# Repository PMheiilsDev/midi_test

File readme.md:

# Midi Controller for Voicemeeter with rp2040

# Setting up Voicemeeter 

 - Menu -> Midi Mapping 
   - Select 'Tiny USB Device' as Input and Output 
   - Use Learn to setup the Buttons or sliders 
   - Press the 'F'-Button so that it is blue 

# Some Comments might be German and English

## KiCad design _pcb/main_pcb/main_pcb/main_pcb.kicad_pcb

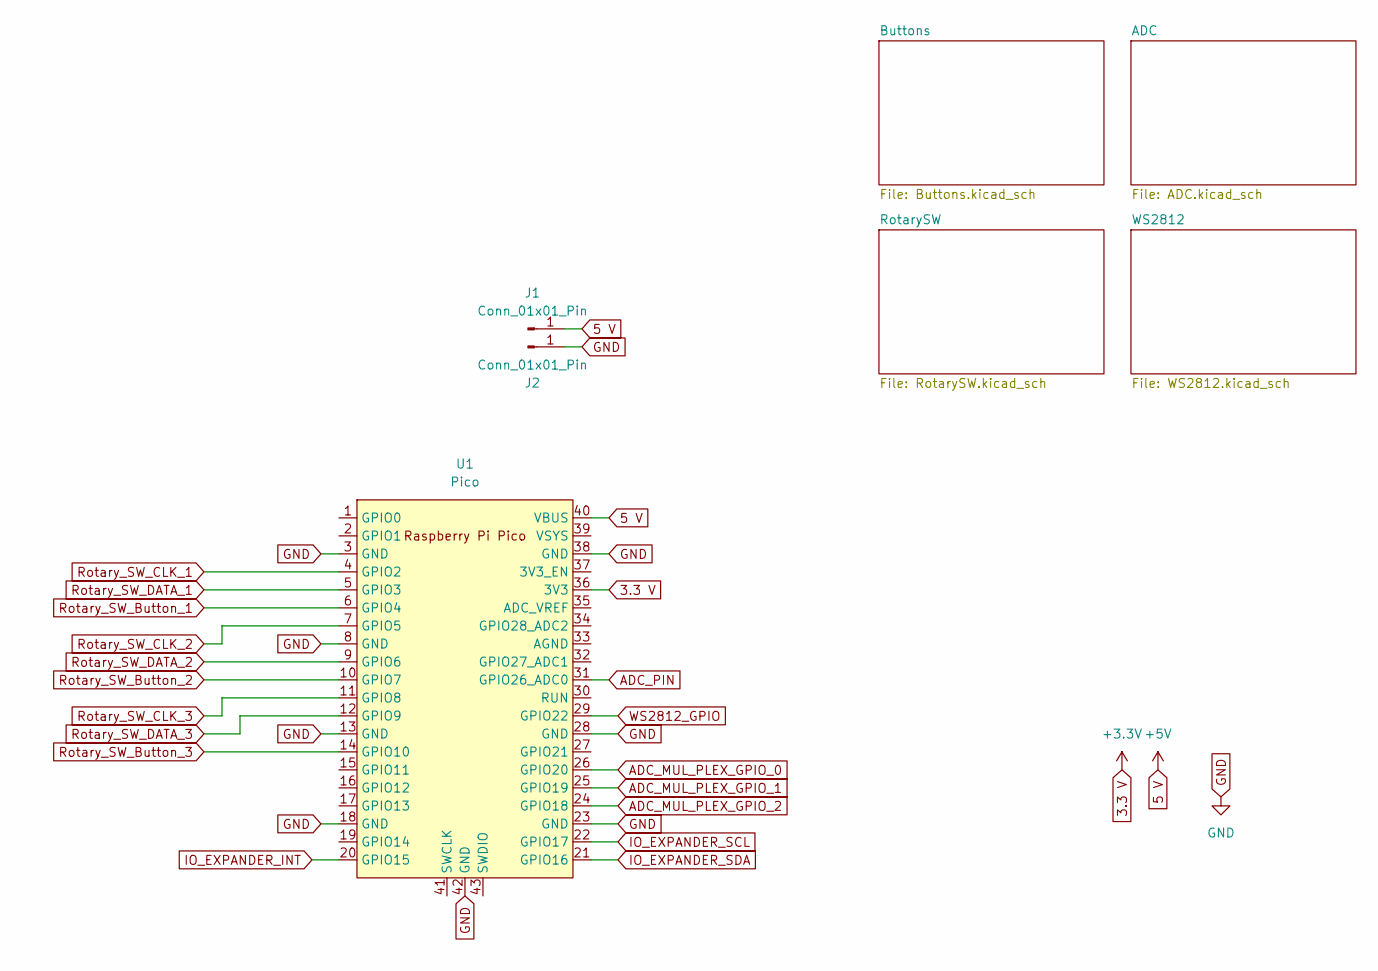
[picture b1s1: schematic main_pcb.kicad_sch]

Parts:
J1, J2: Conn_01x01_Pin; TestPoint_Pad_3.0x3.0mm
U1: Pico; RPi_Pico_SMD_TH

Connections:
3.3 V: U1.36 (3V3); also elsewhere on the board
5 V: J1.1, U1.40 (VBUS); also elsewhere on the board
ADC_MUL_PLEX_GPIO_0: U1.26 (GPIO20); also elsewhere on the board
ADC_MUL_PLEX_GPIO_1: U1.25 (GPIO19); also elsewhere on the board
ADC_MUL_PLEX_GPIO_2: U1.24 (GPIO18); also elsewhere on the board
ADC_PIN: U1.31 (GPIO26_ADC0); also elsewhere on the board
GND: J2.1, U1.3 (GND), U1.8 (GND), U1.13 (GND), U1.18 (GND), U1.23 (GND), U1.28 (GND), U1.38 (GND), U1.42 (GND); also elsewhere on the board
IO_EXPANDER_INT: U1.20 (GPIO15); also elsewhere on the board
IO_EXPANDER_SCL: U1.22 (GPIO17); also elsewhere on the board
IO_EXPANDER_SDA: U1.21 (GPIO16); also elsewhere on the board
Rotary_SW_Button_1: U1.6 (GPIO4); also elsewhere on the board
Rotary_SW_Button_2: U1.10 (GPIO7); also elsewhere on the board
Rotary_SW_Button_3: U1.14 (GPIO10); also elsewhere on the board
Rotary_SW_CLK_1: U1.4 (GPIO2); also elsewhere on the board
Rotary_SW_CLK_2: U1.7 (GPIO5); also elsewhere on the board
Rotary_SW_CLK_3: U1.11 (GPIO8); also elsewhere on the board
Rotary_SW_DATA_1: U1.5 (GPIO3); also elsewhere on the board
Rotary_SW_DATA_2: U1.9 (GPIO6); also elsewhere on the board
Rotary_SW_DATA_3: U1.12 (GPIO9); also elsewhere on the board
WS2812_GPIO: U1.29 (GPIO22); also elsewhere on the board

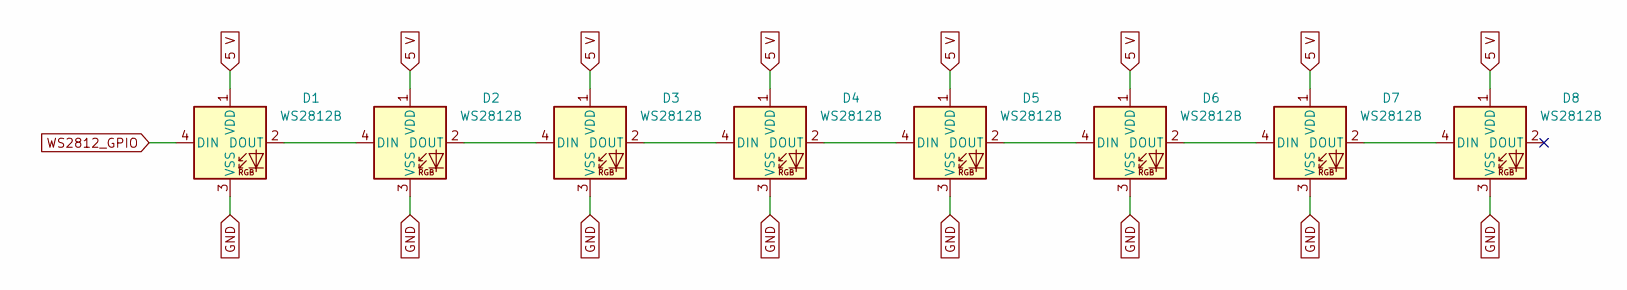
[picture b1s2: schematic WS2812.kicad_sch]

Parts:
D1, D2, D3, D4, D5, D6, D7, D8: WS2812B; LED_WS2812B_PLCC4_5.0x5.0mm_P3.2mm

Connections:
5 V: D1.1 (VDD), D2.1 (VDD), D3.1 (VDD), D4.1 (VDD), D5.1 (VDD), D6.1 (VDD), D7.1 (VDD), D8.1 (VDD); also elsewhere on the board
GND: D1.3 (VSS), D2.3 (VSS), D3.3 (VSS), D4.3 (VSS), D5.3 (VSS), D6.3 (VSS), D7.3 (VSS), D8.3 (VSS); also elsewhere on the board
unnamed: D1.2 (DOUT), D2.4 (DIN)
unnamed: D2.2 (DOUT), D3.4 (DIN)
unnamed: D3.2 (DOUT), D4.4 (DIN)
unnamed: D4.2 (DOUT), D5.4 (DIN)
unnamed: D5.2 (DOUT), D6.4 (DIN)
unnamed: D6.2 (DOUT), D7.4 (DIN)
unnamed: D7.2 (DOUT), D8.4 (DIN)
WS2812_GPIO: D1.4 (DIN); also elsewhere on the board

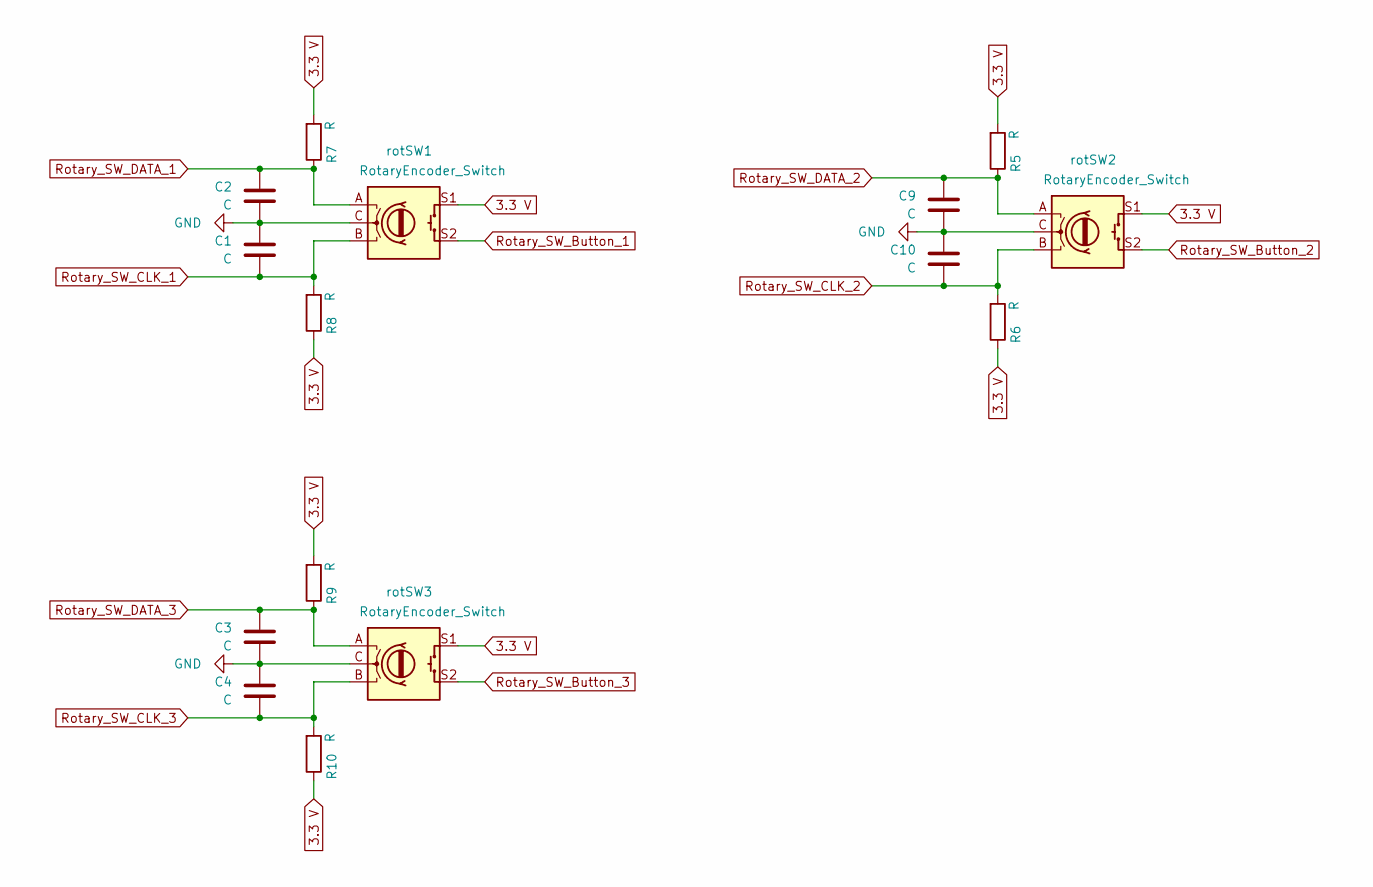
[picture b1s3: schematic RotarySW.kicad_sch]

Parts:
C1, C2, C3, C4, C9, C10: C; C_1206_3216Metric
R5, R6, R7, R8, R9, R10: R; R_1206_3216Metric
rotSW1, rotSW2, rotSW3: RotaryEncoder_Switch; RotaryEncoder_Alps_EC11E-Switch_Vertical_H20mm

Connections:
3.3 V: R5.2, R6.1, R7.2, R8.1, R9.2, R10.1, rotSW1.S1, rotSW2.S1, rotSW3.S1; also elsewhere on the board
GND: C1.1, C2.2, C3.2, C4.1, C9.2, C10.1, rotSW1.C, rotSW2.C, rotSW3.C; also elsewhere on the board
Rotary_SW_Button_1: rotSW1.S2; also elsewhere on the board
Rotary_SW_Button_2: rotSW2.S2; also elsewhere on the board
Rotary_SW_Button_3: rotSW3.S2; also elsewhere on the board
Rotary_SW_CLK_1: C1.2, R8.2, rotSW1.B; also elsewhere on the board
Rotary_SW_CLK_2: C10.2, R6.2, rotSW2.B; also elsewhere on the board
Rotary_SW_CLK_3: C4.2, R10.2, rotSW3.B; also elsewhere on the board
Rotary_SW_DATA_1: C2.1, R7.1, rotSW1.A; also elsewhere on the board
Rotary_SW_DATA_2: C9.1, R5.1, rotSW2.A; also elsewhere on the board
Rotary_SW_DATA_3: C3.1, R9.1, rotSW3.A; also elsewhere on the board

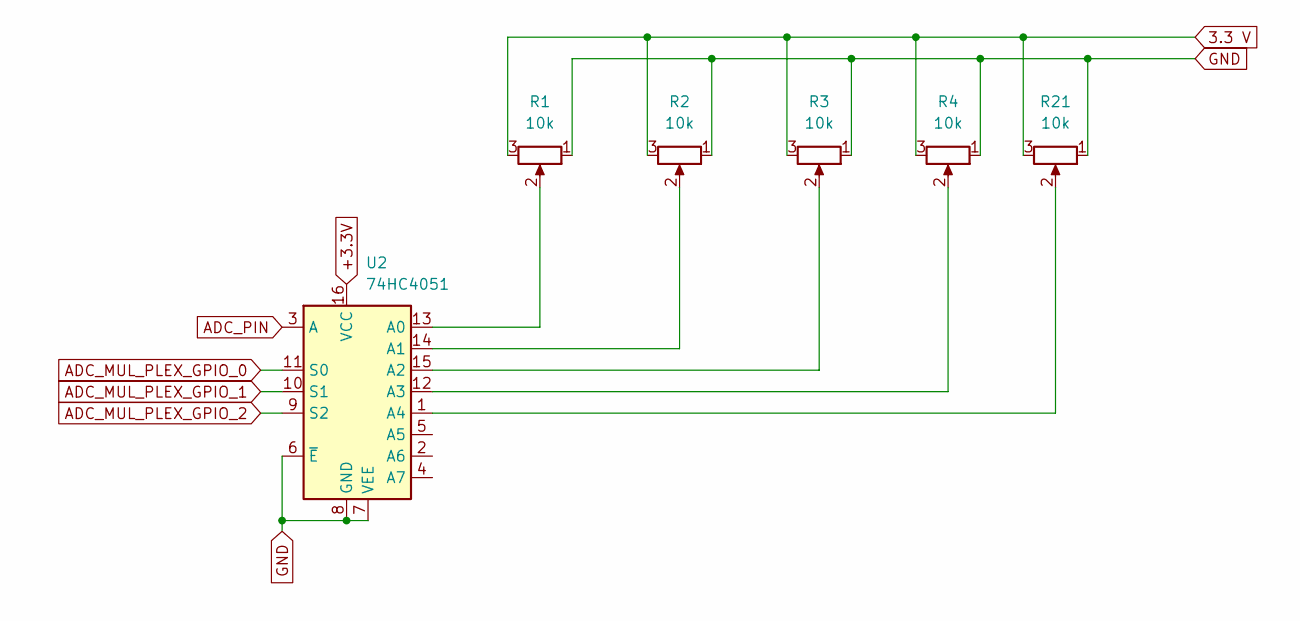
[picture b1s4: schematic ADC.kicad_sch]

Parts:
R1, R2, R3, R4, R21: 10k; Linear_Potentiometer
U2: 74HC4051; DIP-16_W7.62mm

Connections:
3.3 V: R1.3, R2.3, R3.3, R4.3, R21.3, U2.16 (VCC); also elsewhere on the board
ADC_MUL_PLEX_GPIO_0: U2.11 (S0); also elsewhere on the board
ADC_MUL_PLEX_GPIO_1: U2.10 (S1); also elsewhere on the board
ADC_MUL_PLEX_GPIO_2: U2.9 (S2); also elsewhere on the board
ADC_PIN: U2.3 (A); also elsewhere on the board
GND: R1.1, R2.1, R3.1, R4.1, R21.1, U2.6 (~E), U2.7 (VEE), U2.8 (GND); also elsewhere on the board
unnamed: R1.2, U2.13 (A0)
unnamed: R2.2, U2.14 (A1)
unnamed: R3.2, U2.15 (A2)
unnamed: R4.2, U2.12 (A3)
unnamed: R21.2, U2.1 (A4)

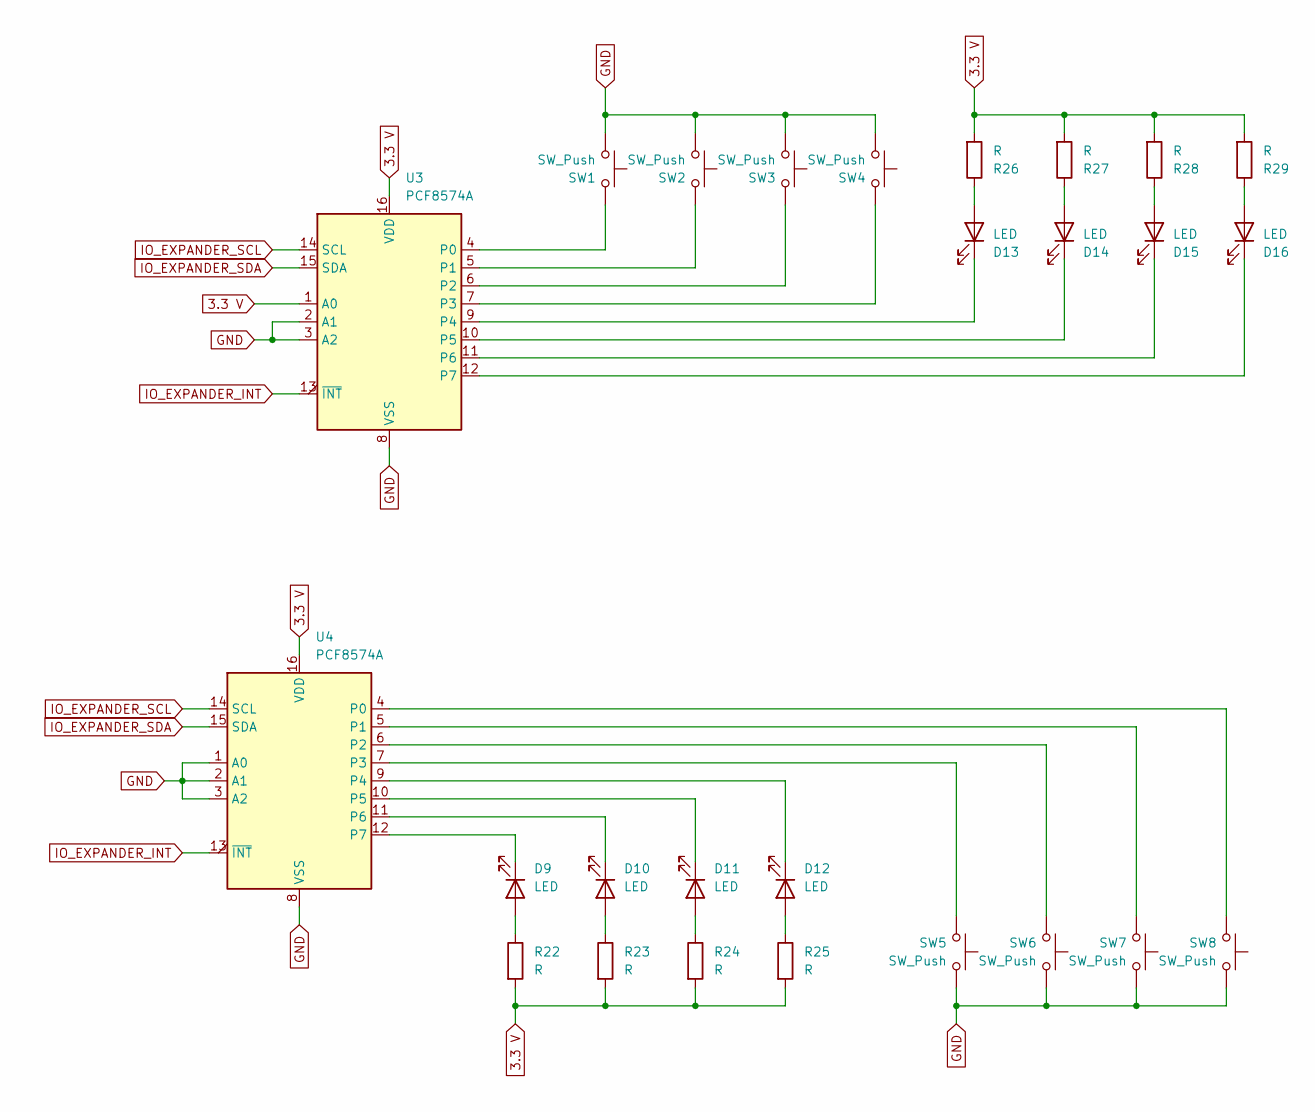
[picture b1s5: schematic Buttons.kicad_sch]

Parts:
D9, D10, D11, D12, D13, D14, D15, D16: LED; LED_Rectangular_W3.9mm_H1.9mm
R22, R23, R24, R25, R26, R27, R28, R29: R; L_1206_3216Metric_Pad1.22x1.90mm_HandSolder
SW1, SW2, SW3, SW4, SW5, SW6, SW7, SW8: SW_Push; SW_Cherry_MX_1.00u_Plate
U3, U4: PCF8574A; DIP-16_W7.62mm

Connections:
3.3 V: R22.2, R23.2, R24.2, R25.2, R26.2, R27.2, R28.2, R29.2, U3.1 (A0), U3.16 (VDD), U4.16 (VDD); also elsewhere on the board
GND: SW1.1, SW2.1, SW3.1, SW4.1, SW5.1, SW6.1, SW7.1, SW8.1, U3.2 (A1), U3.3 (A2), U3.8 (VSS), U4.1 (A0), U4.2 (A1), U4.3 (A2), U4.8 (VSS); also elsewhere on the board
IO_EXPANDER_INT: U3.13 (~INT), U4.13 (~INT); also elsewhere on the board
IO_EXPANDER_SCL: U3.14 (SCL), U4.14 (SCL); also elsewhere on the board
IO_EXPANDER_SDA: U3.15 (SDA), U4.15 (SDA); also elsewhere on the board
unnamed: D9.2 (A), R22.1
unnamed: D9.1 (K), U4.12 (P7)
unnamed: D10.2 (A), R23.1
unnamed: D10.1 (K), U4.11 (P6)
unnamed: D11.2 (A), R24.1
unnamed: D11.1 (K), U4.10 (P5)
unnamed: D12.2 (A), R25.1
unnamed: D12.1 (K), U4.9 (P4)
unnamed: D13.2 (A), R26.1
unnamed: D13.1 (K), U3.9 (P4)
unnamed: D14.2 (A), R27.1
unnamed: D14.1 (K), U3.10 (P5)
unnamed: D15.2 (A), R28.1
unnamed: D15.1 (K), U3.11 (P6)
unnamed: D16.2 (A), R29.1
unnamed: D16.1 (K), U3.12 (P7)
unnamed: SW1.2, U3.4 (P0)
unnamed: SW2.2, U3.5 (P1)
unnamed: SW3.2, U3.6 (P2)
unnamed: SW4.2, U3.7 (P3)
unnamed: SW8.2, U4.4 (P0)
unnamed: SW7.2, U4.5 (P1)
unnamed: SW6.2, U4.6 (P2)
unnamed: SW5.2, U4.7 (P3)

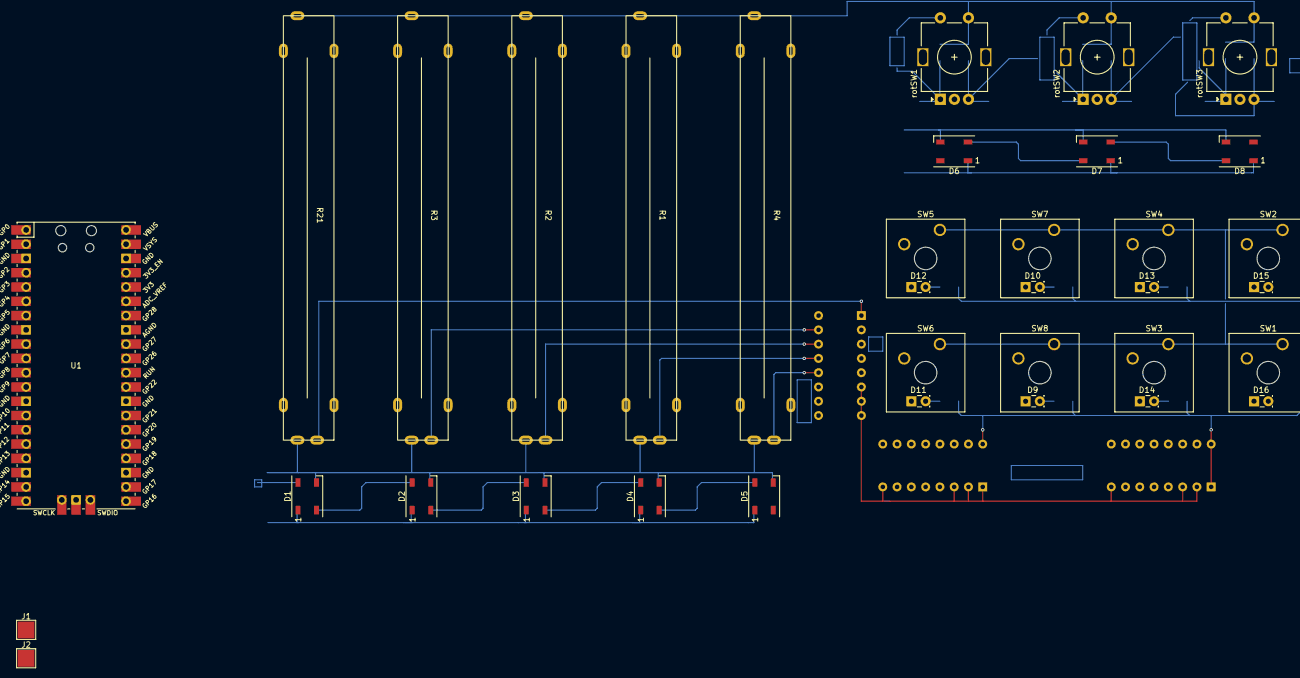
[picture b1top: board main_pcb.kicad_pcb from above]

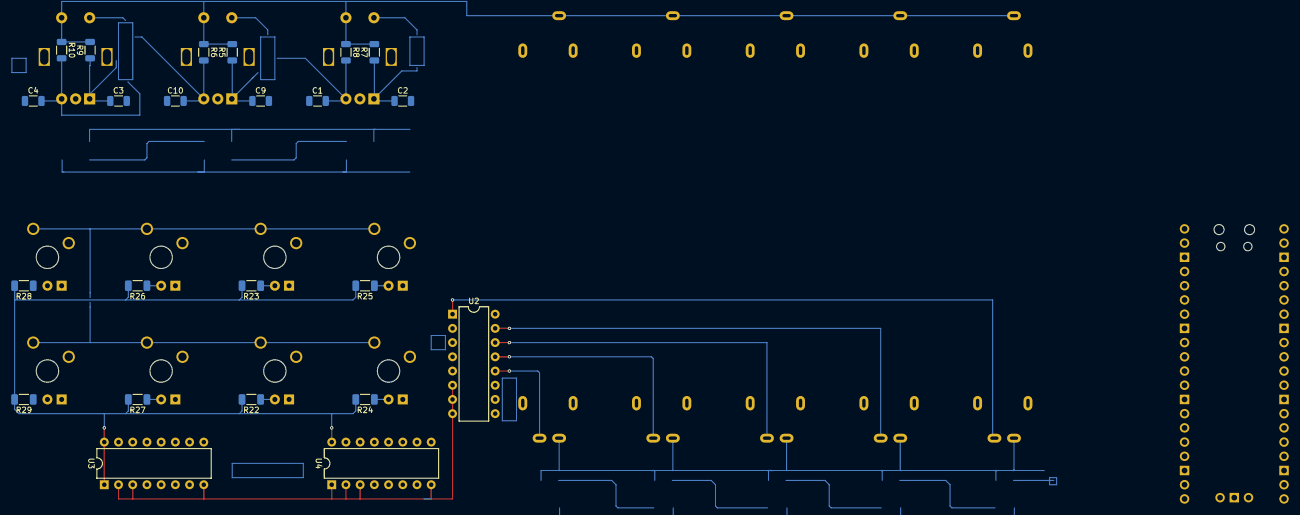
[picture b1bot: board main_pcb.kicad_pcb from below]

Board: 2 copper layers, 58 parts (23 on the bottom side), 56 nets.

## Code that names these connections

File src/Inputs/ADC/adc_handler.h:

#ifndef _ADC_HANDLER_H
#define _ADC_HANDLER_H

#include <inttypes.h>
#include <stdbool.h>

#include "hardware/gpio.h"
#include "hardware/adc.h"


#include "hardware/pwm.h"
#include "tusb.h"

#define MAX_ADC_CHANNELS 5
#define ADC_MUL_LAST_REF_AMT_BITS 4
#define ADC_MUL_LAST_REF_AMT (1 << ADC_MUL_LAST_REF_AMT_BITS) 

#define ADC_MUL_PLEX_GPIO_0 21
#define ADC_MUL_PLEX_GPIO_1 20
#define ADC_MUL_PLEX_GPIO_2 19

typedef struct 
{
    uint8_t pin;
    uint8_t note;
    uint8_t is_mul_plex: 1, mul_plex_channel : 3; // assuming that the multiplexer has 3 pins for channel selection 
    uint8_t mul_plex[3];
    uint16_t result;
    uint16_t result_pref; 
    uint8_t res_7_bit;
    uint8_t num_reads;
} 
adc_channel_t;

extern adc_channel_t adc_channels[MAX_ADC_CHANNELS];

/// @brief setting up all necessary ADCs from cdc_channels and starting timer to call adc_task 
void adc_setup(void);

/// @brief handling next ADC from adc_channels 
bool adc_task( repeating_timer_t *rt );

/// @brief converting a GPIO pin to an ADC channel 
/// @param gpio GPIO pin number 
/// @return ADC channel number 
static inline int gpio_to_adc_channel(uint gpio);

/// @brief set the value of the gpio pins set in the adc_channel
/// @param adc_channel pointer to the adc_channel_t 
void adc_set_mul_plex_gpios( adc_channel_t *adc_channel );

#endif


// ADC ideas
// create a reapeating timer and read the adc value every so often
//
// create a function that can simulate a Highpass filter by interpolating 
// filter values that are off from average 
//  - this might make add delay


// ADC TODO 
// - add support for using analog multiplexer to read multiple analog inputs

// ((( it might be possible to check if a multiplexer is connected by connecting one of the 8 channels to a fixed level )))

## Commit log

2024-11-20 example working
2024-11-21 first test working
2024-11-21 working adc to pwm ; not working in voice meeter
2024-11-22 some changes to timings
2024-11-23 working with hardware debounce
2024-11-29 debugger working
2024-11-29 removed map function
2025-02-09 added gitignore file
2025-02-09 gitignore build
2025-02-09 added readme file
2025-02-09 todo file
2025-02-09 todo list update
2025-02-09 Button init
2025-02-09 Button doing nothing yet
2025-02-09 rotary sw fixes removed feedback
2025-02-09 Changed so that range of poti can be used for usefull area
2025-02-09 added input reader with python
2025-02-09 added midi send to rp2040 tests
2025-02-09 does recieve something with voicemeeter
2025-02-09 uart debugging not working
2025-02-09 see todo updated to test feedback to rp2040 with voicemeeter
2025-02-14 ui program with chatgpt
2025-02-14 changed updating of dropdown lists
2025-02-14 not as i want it to be
2025-02-14 refresh buttons not scaling
2025-02-14 selecting works when only one present
2025-02-14 adding input device change message
2025-02-14 changed to use text and dupe when one
2025-02-14 using the activated works at all changes
2025-02-14 device selection working
2025-02-14 added #regions but listner no longer working
2025-02-14 one region added
2025-02-14 added [ -> ] and [ <- ]
2025-02-14 clear button
2025-02-14 made it bolt
2025-02-14 Disconnect Buttons
2025-02-14 both disconnects working
2025-02-14 todo
2025-02-15 why not working
2025-02-15 was working just had to replug
2025-02-27 logging the data as strings
2025-02-27 readme
2025-02-28 move main c file
2025-02-28 moved rot sw functions to own files
2025-02-28 variabels added
2025-02-28 fixed error
2025-02-28 moved midi handler to other files
2025-02-28 moved adc handler
2025-02-28 renamed folder
2025-02-28 moved to new files
2025-02-28 moved led functions
2025-02-28 changed to led handler
2025-02-28 changed adc scaling
2025-03-02 led setup functions
2025-03-02 process all up/ down interupts for rotary sw
2025-03-02 extended to more than one rot sw switch with AI
2025-03-02 foramtion and to const uint = 2
2025-03-02 working
2025-03-03 gpio to adc channel
2025-03-03 ideas update average implementation
2025-03-04 added ws2812 files
2025-03-04 ws2812 testing timing
2025-03-05 testing reset time
2025-03-05 added usefull ws2812 handler functions and structs
2025-03-05 removed tests from init
2025-03-07 changed to update at ever change not only every second
2025-03-07 removed pwm pin
2025-03-07 changed to work with multiple adc pins
2025-03-07 added comments
2025-03-07 added adc multiplexer support initialisation
2025-03-07 added multiplexer function to adc_task
2025-03-07 todo added note
2025-03-07 added to header file
2025-03-08 testing how long a loop takes .5 ms without adc sleep time
2025-03-08 added kiCAD Project
2025-03-08 added lib for mx switches
2025-03-08 added own footprint lib for potentiometer
2025-03-08 added libraries to project
2025-03-08 changed to work with relative paths
2025-03-08 added cache file to gitignore
2025-03-08 added .zip files to git ignore
2025-03-08 automatic changes by kicad
2025-03-08 added pi pico footprint library
2025-03-08 changed to rel path
2025-03-08 added pi pico symbol from lib
2025-03-08 changes to pcb
2025-03-08 added io expander and rotSW only ws2812 missing
2025-03-09 added WS2812
2025-03-09 update to gitignore for lock file
2025-03-09 for now the last commit for pcb as buying pcb is too expensive
2025-03-10 added files to project
2025-03-10 settings update
2025-03-10 testing pcf8575
2025-03-10 this uses all pins as input
2025-03-11 added functions declarations with comments
2025-03-11 added storage ints for the io expander data
2025-03-11 added a few functions
2025-03-11 should be complete untested though
2025-03-11 set the values to high z input at init
2025-03-11 not working maybe bit order wrong ??
2025-03-11 all pins OUTPUT working fine, exept the one o was testing with (maybe i broke pin P10 ???)
2025-03-11 input not working as planned
2025-03-11 added todo list
2025-03-11 set function is working as planned
2025-03-11 the same as set function so its working
2025-03-11 fixed typo
2025-03-11 writing works as expected
2025-03-11 seams to be working as expected only P10(pin 8) not working properly
2025-03-11 working button toggleing a led
2025-03-11 removed error state from get so now working as gpio_put( not gpio_get )
2025-03-12 changed so that pins are usable for io expander
2025-03-12 ioexpander working with debug functions in it
2025-03-12 for handling IOexpander write other files (io exp handler)
2025-03-12 adc via mul plex working
2025-03-12 created a main irq handler function as only one function can be set per Core not one per gpio
2025-03-12 io exp and adc working together without i2c never returning
2025-03-12 adc working with three via mul plex and one directly
2025-03-12 added leds to io expander
2025-03-12 optimising irq functions
2025-03-12 added ioexpander handler files
2025-03-12 io expander working via midi in voicemeeter but it shows some strange behaivior as if voicemeeter tryes to fix the software change when state is changed from voice meeter
2025-03-16 renamed ws2812 files ( removed handler )
2025-03-16 settings and header guard renamed
2025-03-16 added handler files
2025-03-16 added array of the ws2812 elements
2025-03-16 kind of working but ws2812_update wastes alot of time when called every loop
2025-03-16 added parameter to ws2812 update
2025-03-16 working color picker made with chatgpt
2025-03-16 changed adc mapping
2025-03-16 fixed formation
2025-03-19 added Rot SW simulation file
2025-03-21 hardware prototype working ( rot sw and io expander )
2025-03-29 testing the value set by voice meeter: working good
2025-03-29 had to disable adcs as they where floating in hardware setup
2025-03-30 feedback for buttons also working
2025-03-30 this removes all the flickering from the adc result that is sent
2025-03-31 added comments and prototype
2025-03-31 this does work but has the problem of skipping one step when actually wanting to change the direction so when the manted movement is 100->101->100 the last 100 is not sent as it was there in the last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
2025-03-31 this might be a dead end see NOTE
2025-03-31 this seams to have fixed all the adc flickering problems
2025-04-20 changed to hardware
2025-04-20 rewired rot sw curcits to new plans reduced to only 3
2025-04-20 removed 4th rot sw from pico
2025-04-20 removed all pcb plans
2025-04-20 removed 0 pad name to remove warning
2025-04-20 moved to two pcf8574 instead of pcf8575
2025-04-20 bauteile sortiert
2025-04-20 both pcf an in and out
2025-04-20 positoned all but pico
2025-04-20 changed ICs to THT
2025-04-20 position of pico not really clear
2025-04-21 changed 3.3 V and 0 V so that it is correct
2025-04-21 switches the i2c addresses so that its better on pcb
2025-04-21 alle anderen Verbindungen mit Lackdraht
2025-04-30 changed to fit the hardware
2025-04-30 changed to work with two pcf8574 instead of one pcf8575 the solution always i2c's to both addresses that could be reduced when writing not when listening though
2025-04-30 changed to test all the buttons (hardware working)
2025-04-30 this makes all leds blink
2025-05-03 changed the pins to fit possible hardware
2025-05-09 added notes for midi elements
2025-05-14 changed pins and configs to used hardware
2025-05-14 removed some debug functionality
2025-05-14 i believe to have found the correct pin combinations manually
2025-05-14 removed the debug functions again
2025-05-14 also removed from main
2025-05-14 as far as i know this is the right configuration for the hardware
2025-05-14 all the ioexpander buttons and pins work with each other and are sent via midi
2025-05-15 this works with the buttons when turning on and off from button then on from software it is not send seams to be a voicemeeter error
2025-08-15 fixed slider to led mapping
2025-08-15 todo upodate
2025-08-15 todo update
2025-08-15 this removes the flickering problem i had
2025-08-15 not working
    this callback thing might be a good idea
2025-08-15 conly count one edge as hardware limits that "mit harten Rasterpositionen"
2025-08-15 use changed to deside if has to be send add inverted config function
